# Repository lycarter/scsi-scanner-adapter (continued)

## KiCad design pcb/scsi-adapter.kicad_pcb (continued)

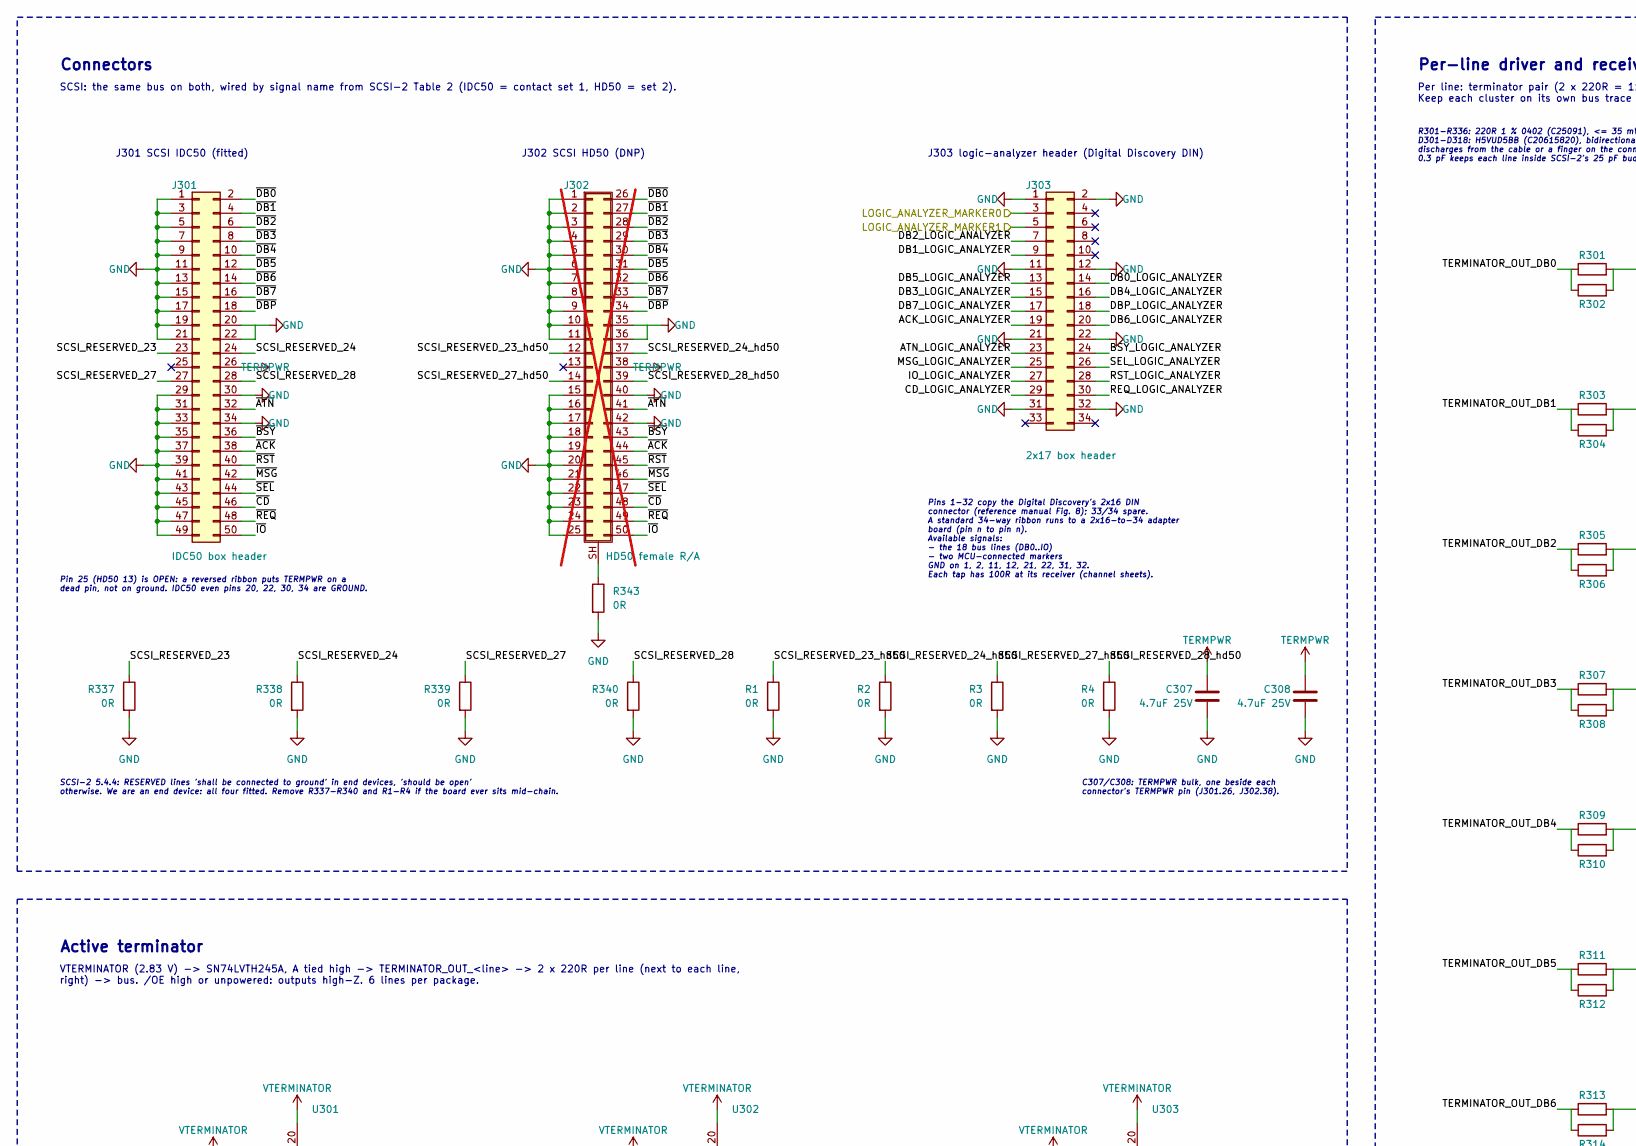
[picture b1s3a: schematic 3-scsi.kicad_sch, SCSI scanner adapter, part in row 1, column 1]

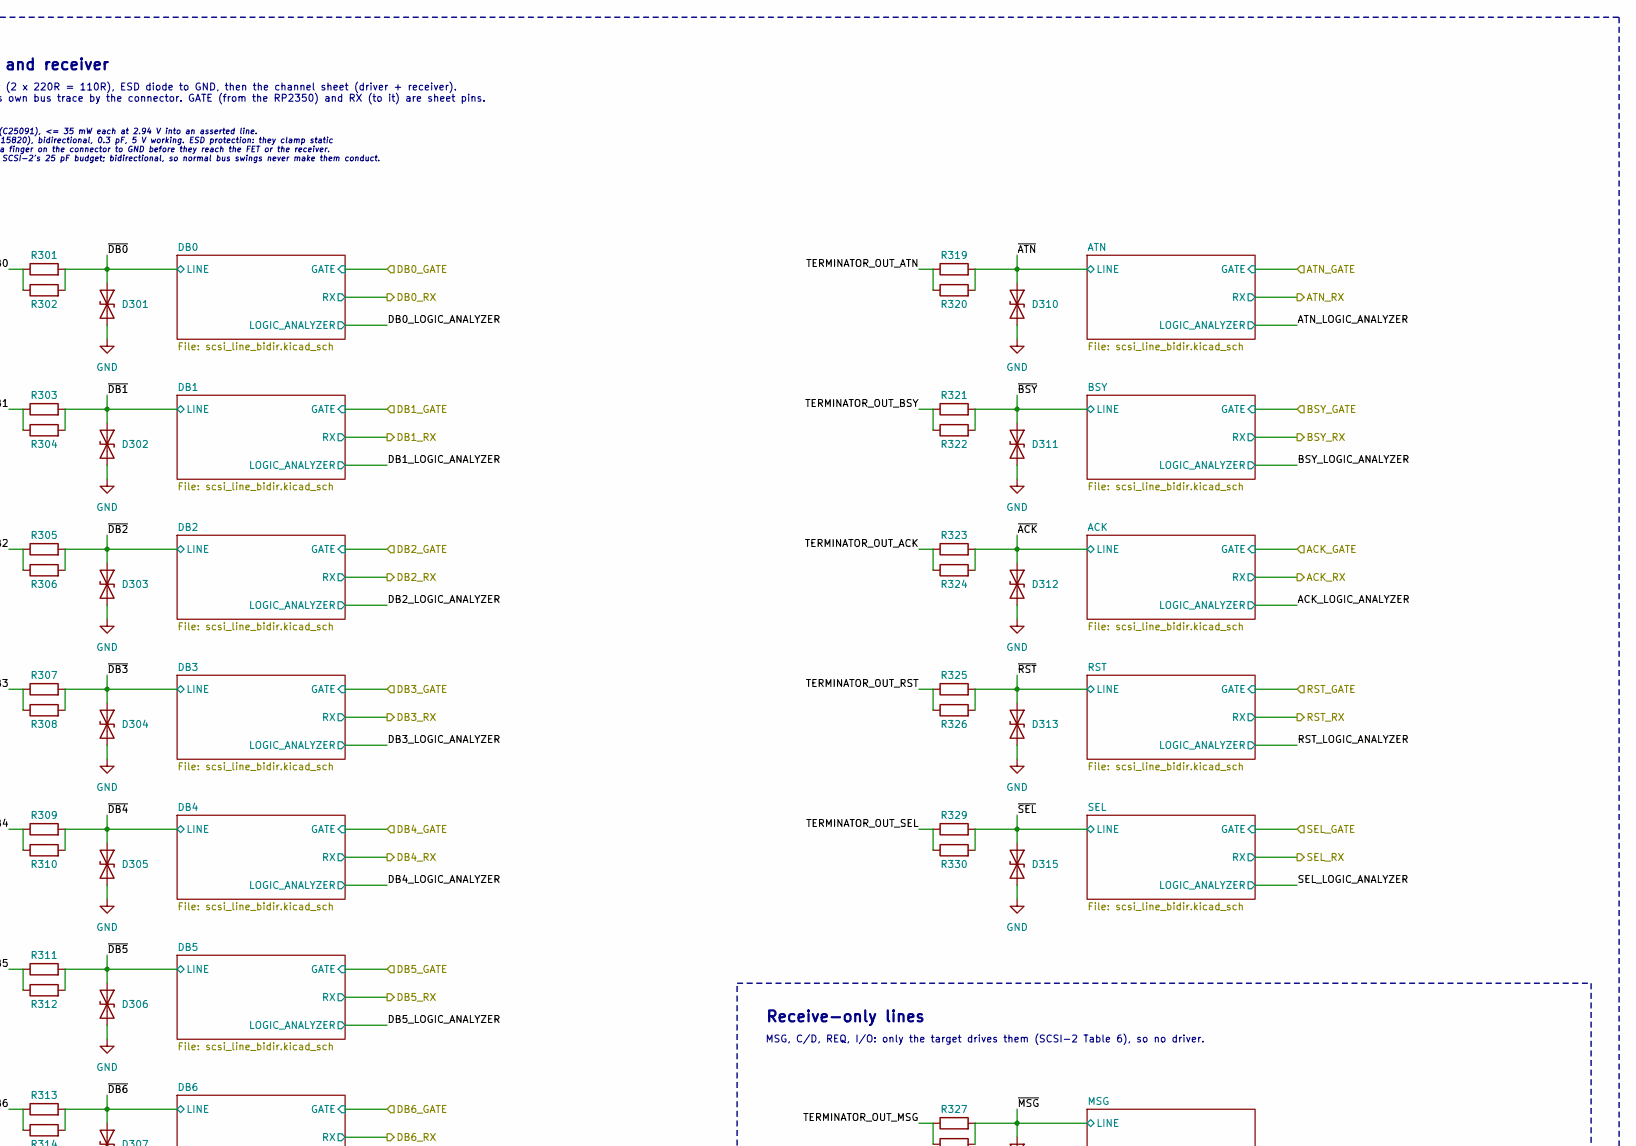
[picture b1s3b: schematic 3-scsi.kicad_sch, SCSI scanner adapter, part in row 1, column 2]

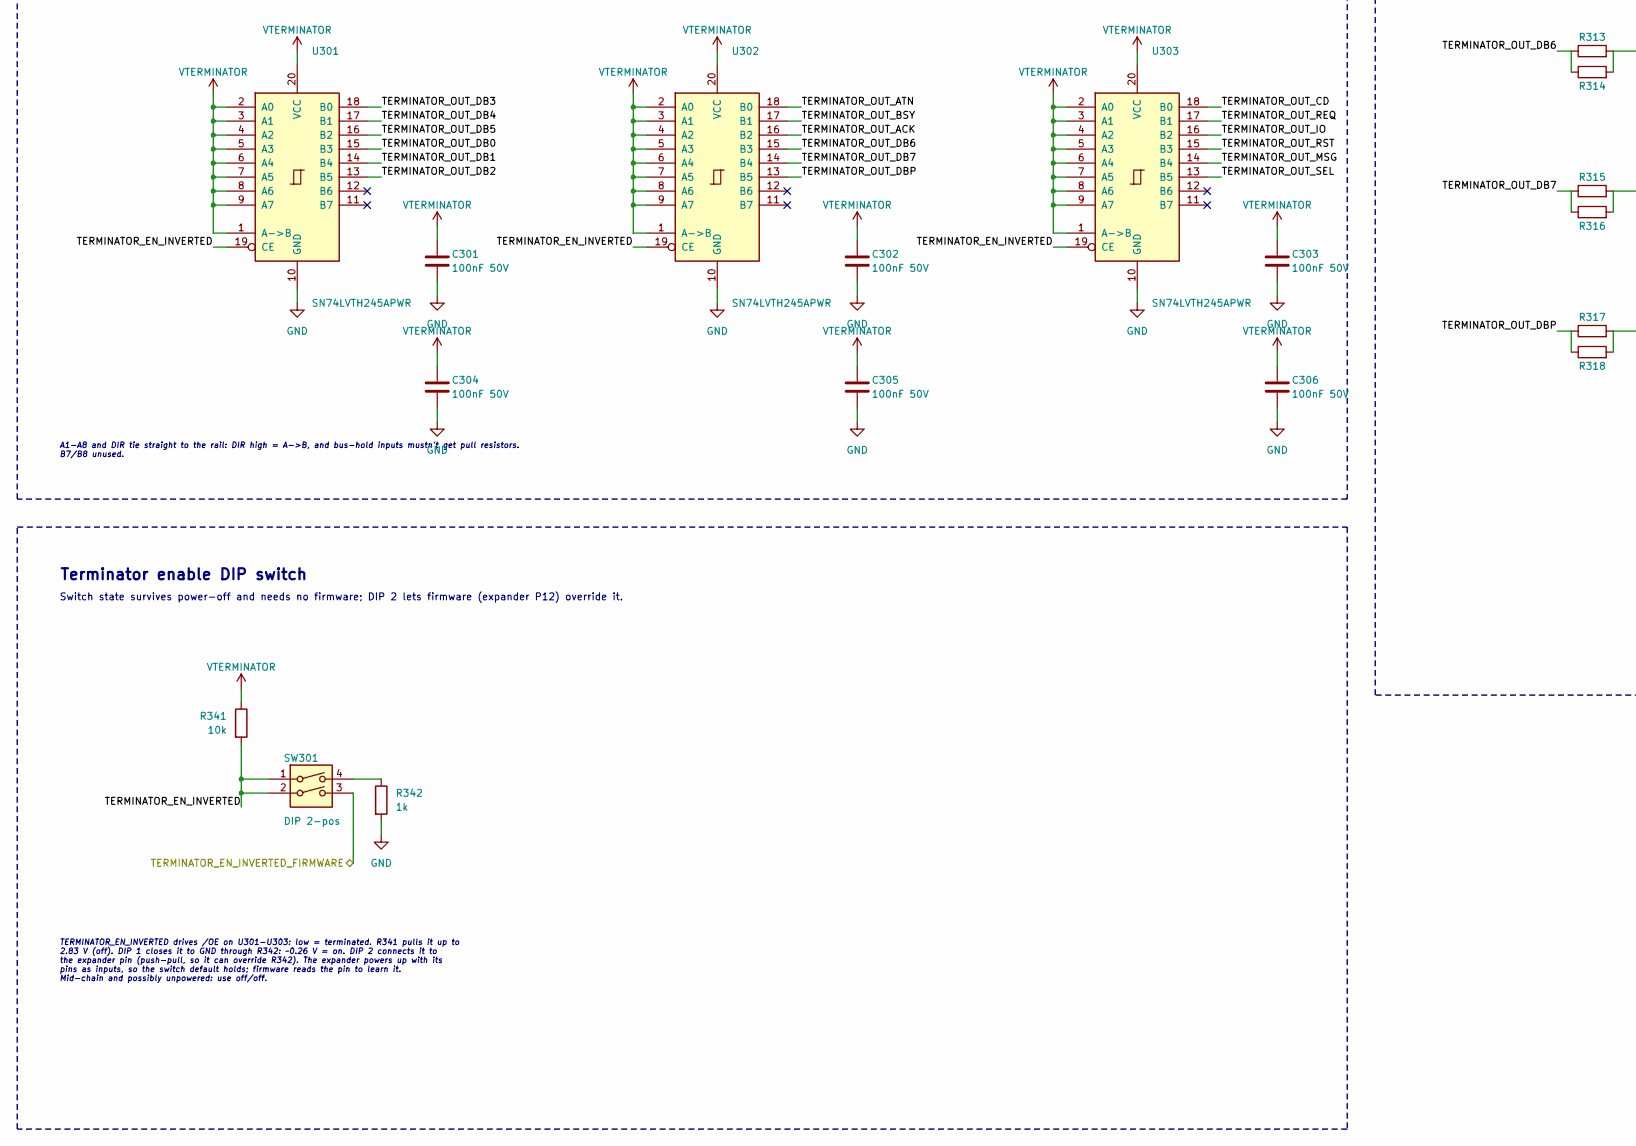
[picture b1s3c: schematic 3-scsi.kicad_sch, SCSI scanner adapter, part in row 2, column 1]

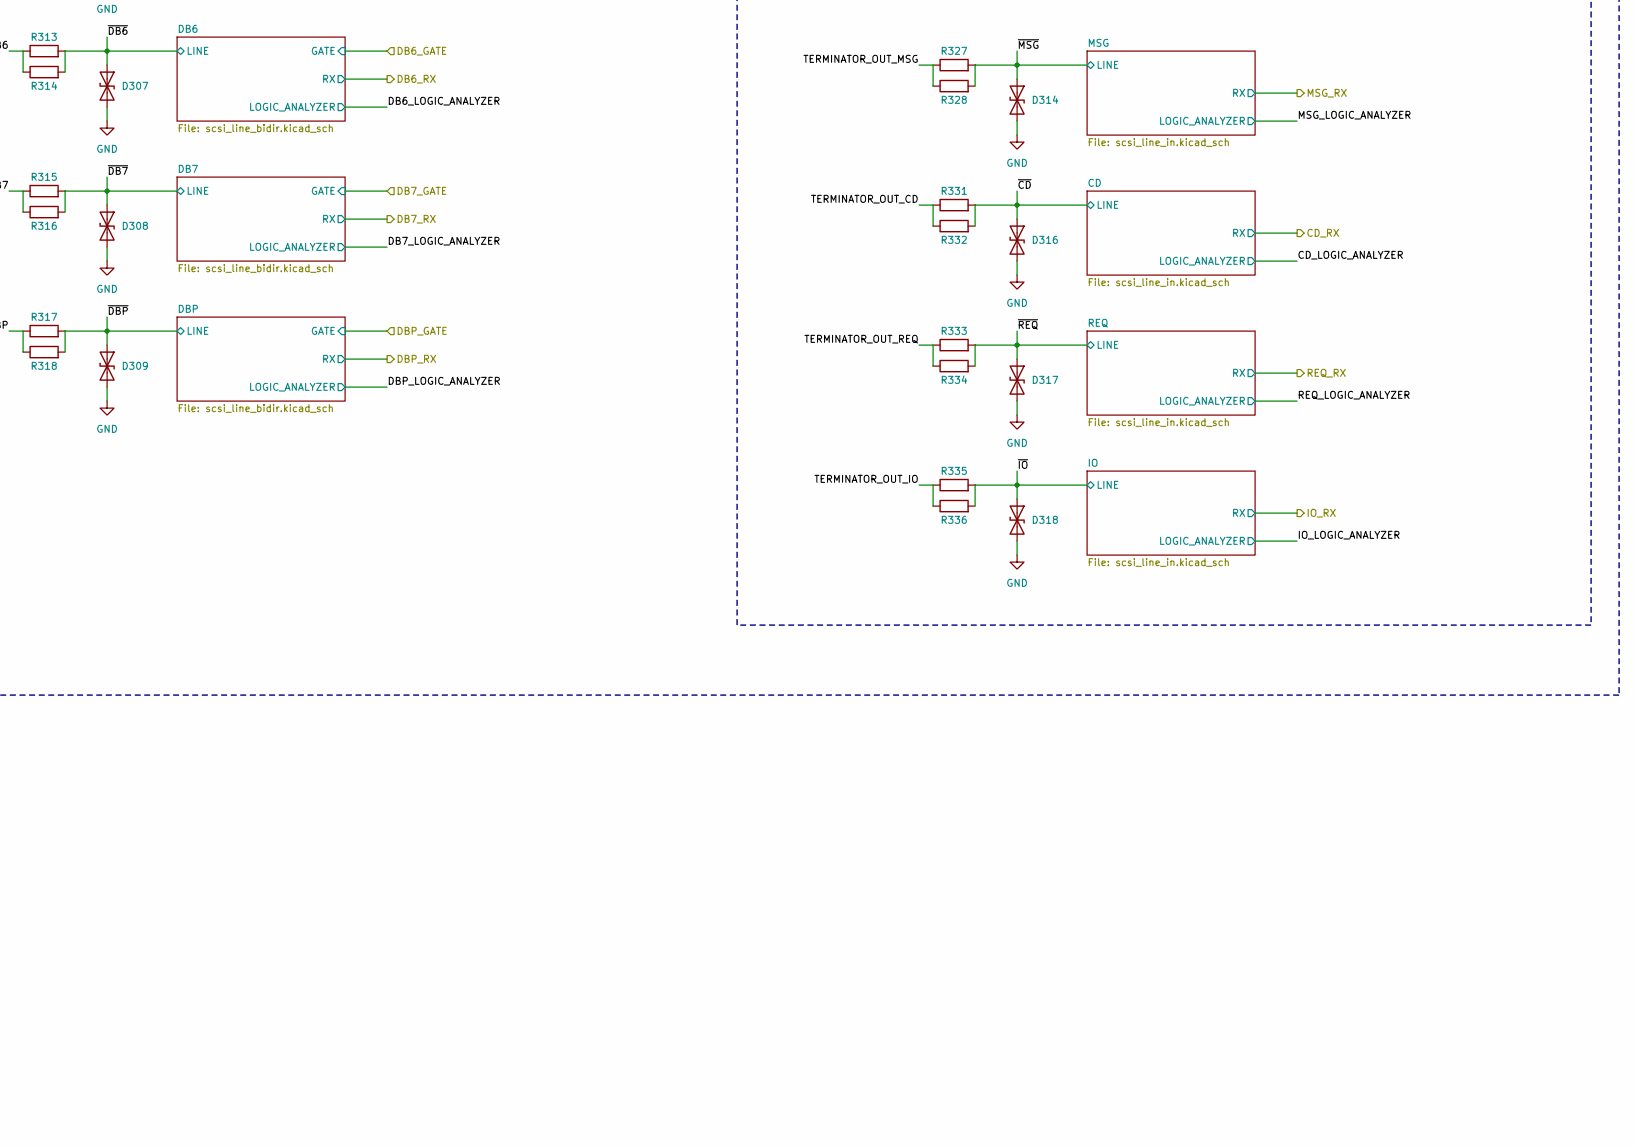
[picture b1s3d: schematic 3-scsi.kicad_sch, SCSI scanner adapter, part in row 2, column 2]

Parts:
C301, C302, C303, C304, C305, C306: 100nF 50V; C_0402_1005Metric; LCSC C307331
C307, C308: 4.7uF 25V; C_0805_2012Metric; LCSC C1779
D301, D302, D303, D304, D305, D306, D307, D308, D309, D310, D311, D312, D313, D314, D315, D316, D317, D318: H5VUD5BB; D_SOD-523; LCSC C20615820
J301: IDC50 box header; IDC-Header_2x25_P2.54mm_Vertical; LCSC C30006
J302: HD50 female R/A; TE_AMPLIMITE-050_5787082-5_50pos_P1.27mm_Horizontal; not fitted
J303: 2x17 box header; IDC-Header_2x17_P2.54mm_Vertical; LCSC C20920
R1, R2, R3, R4, R337, R338, R339, R340, R343: 0R; R_0402_1005Metric; LCSC C17168
R301, R302, R303, R304, R305, R306, R307, R308, R309, R310, R311, R312, R313, R314, R315, R316, R317, R318, R319, R320, R321, R322, R323, R324, R325, R326, R327, R328, R329, R330, R331, R332, R333, R334, R335, R336: 220R; R_0402_1005Metric; LCSC C25091
R341: 10k; R_0402_1005Metric; LCSC C25744
R342: 1k; R_0402_1005Metric; LCSC C11702
SW301: DIP 2-pos; SW_DIP_SPSTx02_Slide_SHOUHAN_2.54-2P-TPGT_W8.8mm_P2.54mm; LCSC C6331180
U301, U302, U303: SN74LVTH245APWR; TSSOP-20_4.4x6.5mm_P0.65mm; LCSC C2652121

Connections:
/LOGIC_ANALYZER_MARKER0: J303.3; also elsewhere on the board
/LOGIC_ANALYZER_MARKER1: J303.5; also elsewhere on the board
/TERMINATOR_EN_INVERTED_FIRMWARE: SW301.3; also elsewhere on the board
/scsi/ACK_LOGIC_ANALYZER: J303.19; also elsewhere on the board
/scsi/ATN_LOGIC_ANALYZER: J303.23; also elsewhere on the board
/scsi/BSY_LOGIC_ANALYZER: J303.24; also elsewhere on the board
/scsi/CD_LOGIC_ANALYZER: J303.29; also elsewhere on the board
/scsi/DB0_LOGIC_ANALYZER: J303.14; also elsewhere on the board
/scsi/DB1_LOGIC_ANALYZER: J303.9; also elsewhere on the board
/scsi/DB2_LOGIC_ANALYZER: J303.7; also elsewhere on the board
/scsi/DB3_LOGIC_ANALYZER: J303.15; also elsewhere on the board
/scsi/DB4_LOGIC_ANALYZER: J303.16; also elsewhere on the board
/scsi/DB5_LOGIC_ANALYZER: J303.13; also elsewhere on the board
/scsi/DB6_LOGIC_ANALYZER: J303.20; also elsewhere on the board
/scsi/DB7_LOGIC_ANALYZER: J303.17; also elsewhere on the board
/scsi/DBP_LOGIC_ANALYZER: J303.18; also elsewhere on the board
/scsi/IO_LOGIC_ANALYZER: J303.27; also elsewhere on the board
/scsi/MSG_LOGIC_ANALYZER: J303.25; also elsewhere on the board
/scsi/REQ_LOGIC_ANALYZER: J303.30; also elsewhere on the board
/scsi/RST_LOGIC_ANALYZER: J303.28; also elsewhere on the board
/scsi/SCSI_RESERVED_23: J301.23, R337.1
/scsi/SCSI_RESERVED_23_hd50: J302.12, R1.1
/scsi/SCSI_RESERVED_24: J301.24, R338.1
/scsi/SCSI_RESERVED_24_hd50: J302.37, R2.1
/scsi/SCSI_RESERVED_27: J301.27, R339.1
/scsi/SCSI_RESERVED_27_hd50: J302.14, R3.1
/scsi/SCSI_RESERVED_28: J301.28, R340.1
/scsi/SCSI_RESERVED_28_hd50: J302.39, R4.1
/scsi/SEL_LOGIC_ANALYZER: J303.26; also elsewhere on the board
/scsi/TERMINATOR_EN_INVERTED: R341.2, SW301.1, SW301.2, U301.19 (CE), U302.19 (CE), U303.19 (CE)
/scsi/TERMINATOR_OUT_ACK: R323.1, R324.1, U302.16 (B2)
/scsi/TERMINATOR_OUT_ATN: R319.1, R320.1, U302.18 (B0)
/scsi/TERMINATOR_OUT_BSY: R321.1, R322.1, U302.17 (B1)
/scsi/TERMINATOR_OUT_CD: R331.1, R332.1, U303.18 (B0)
/scsi/TERMINATOR_OUT_DB0: R301.1, R302.1, U301.15 (B3)
/scsi/TERMINATOR_OUT_DB1: R303.1, R304.1, U301.14 (B4)
/scsi/TERMINATOR_OUT_DB2: R305.1, R306.1, U301.13 (B5)
/scsi/TERMINATOR_OUT_DB3: R307.1, R308.1, U301.18 (B0)
/scsi/TERMINATOR_OUT_DB4: R309.1, R310.1, U301.17 (B1)
/scsi/TERMINATOR_OUT_DB5: R311.1, R312.1, U301.16 (B2)
/scsi/TERMINATOR_OUT_DB6: R313.1, R314.1, U302.15 (B3)
/scsi/TERMINATOR_OUT_DB7: R315.1, R316.1, U302.14 (B4)
/scsi/TERMINATOR_OUT_DBP: R317.1, R318.1, U302.13 (B5)
/scsi/TERMINATOR_OUT_IO: R335.1, R336.1, U303.16 (B2)
/scsi/TERMINATOR_OUT_MSG: R327.1, R328.1, U303.14 (B4)
/scsi/TERMINATOR_OUT_REQ: R333.1, R334.1, U303.17 (B1)
/scsi/TERMINATOR_OUT_RST: R325.1, R326.1, U303.15 (B3)
/scsi/TERMINATOR_OUT_SEL: R329.1, R330.1, U303.13 (B5)
/scsi/~ACK: D312.1 (A1), J301.38, J302.44, R323.2, R324.2; also elsewhere on the board
/scsi/~ATN: D310.1 (A1), J301.32, J302.41, R319.2, R320.2; also elsewhere on the board
/scsi/~BSY: D311.1 (A1), J301.36, J302.43, R321.2, R322.2; also elsewhere on the board
/scsi/~CD: D316.1 (A1), J301.46, J302.48, R331.2, R332.2; also elsewhere on the board
/scsi/~DB0: D301.1 (A1), J301.2, J302.26, R301.2, R302.2; also elsewhere on the board
/scsi/~DB1: D302.1 (A1), J301.4, J302.27, R303.2, R304.2; also elsewhere on the board
/scsi/~DB2: D303.1 (A1), J301.6, J302.28, R305.2, R306.2; also elsewhere on the board
/scsi/~DB3: D304.1 (A1), J301.8, J302.29, R307.2, R308.2; also elsewhere on the board
/scsi/~DB4: D305.1 (A1), J301.10, J302.30, R309.2, R310.2; also elsewhere on the board
/scsi/~DB5: D306.1 (A1), J301.12, J302.31, R311.2, R312.2; also elsewhere on the board
/scsi/~DB6: D307.1 (A1), J301.14, J302.32, R313.2, R314.2; also elsewhere on the board
/scsi/~DB7: D308.1 (A1), J301.16, J302.33, R315.2, R316.2; also elsewhere on the board
/scsi/~DBP: D309.1 (A1), J301.18, J302.34, R317.2, R318.2; also elsewhere on the board
/scsi/~IO: D318.1 (A1), J301.50, J302.50, R335.2, R336.2; also elsewhere on the board
/scsi/~MSG: D314.1 (A1), J301.42, J302.46, R327.2, R328.2; also elsewhere on the board
/scsi/~REQ: D317.1 (A1), J301.48, J302.49, R333.2, R334.2; also elsewhere on the board
/scsi/~RST: D313.1 (A1), J301.40, J302.45, R325.2, R326.2; also elsewhere on the board
/scsi/~SEL: D315.1 (A1), J301.44, J302.47, R329.2, R330.2; also elsewhere on the board
GND: C301.2, C302.2, C303.2, C304.2, C305.2, C306.2, C307.2, C308.2, D301.2 (A2), D302.2 (A2), D303.2 (A2), D304.2 (A2), D305.2 (A2), D306.2 (A2), D307.2 (A2), D308.2 (A2), D309.2 (A2), D310.2 (A2), D311.2 (A2), D312.2 (A2), D313.2 (A2), D314.2 (A2), D315.2 (A2), D316.2 (A2), D317.2 (A2), D318.2 (A2), J301.1, J301.3, J301.5, J301.7, J301.9, J301.11, J301.13, J301.15, J301.17, J301.19, J301.20, J301.21, J301.22, J301.29, J301.30, J301.31, J301.33, J301.34, J301.35, J301.37, J301.39, J301.41, J301.43, J301.45, J301.47, J301.49, J302.1, J302.2, J302.3, J302.4, J302.5, J302.6, J302.7, J302.8, J302.9, J302.10, J302.11, J302.15, J302.16, J302.17, J302.18, J302.19, J302.20, J302.21, J302.22, J302.23, J302.24, J302.25, J302.35, J302.36, J302.40, J302.42, J303.1, J303.2, J303.11, J303.12, J303.21, J303.22, J303.31, J303.32, R1.2, R2.2, R3.2, R4.2, R337.2, R338.2, R339.2, R340.2, R342.2, R343.2, U301.10 (GND), U302.10 (GND), U303.10 (GND); also elsewhere on the board
unnamed: J302.SH (Shield), R343.1
unnamed: R342.1, SW301.4
TERMPWR: C307.1, C308.1, J301.26, J302.38; also elsewhere on the board
VTERMINATOR: C301.1, C302.1, C303.1, C304.1, C305.1, C306.1, R341.1, U301.1 (A->B), U301.2 (A0), U301.3 (A1), U301.4 (A2), U301.5 (A3), U301.6 (A4), U301.7 (A5), U301.8 (A6), U301.9 (A7), U301.20 (VCC), U302.1 (A->B), U302.2 (A0), U302.3 (A1), U302.4 (A2), U302.5 (A3), U302.6 (A4), U302.7 (A5), U302.8 (A6), U302.9 (A7), U302.20 (VCC), U303.1 (A->B), U303.2 (A0), U303.3 (A1), U303.4 (A2), U303.5 (A3), U303.6 (A4), U303.7 (A5), U303.8 (A6), U303.9 (A7), U303.20 (VCC); also elsewhere on the board

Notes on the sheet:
Pins 1-32 copy the Digital Discovery's 2x16 DIN connector (reference manual Fig. 8); 33/34 spare. A standard 34-way ribbon runs to a 2x16-to-34 adapter board (pin n to pin n). Available signals: - the 18 bus lines (DB0..IO) - two MCU-connected markers GND on 1, 2, 11, 12, 21, 22, 31, 32. Each tap h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
SCSI: the same bus on both, wired by signal name from SCSI-2 Table 2 (IDC50 = contact set 1, HD50 = set 2).
Receive-only lines
Connectors
Active terminator
R301-R336: 220R 1 % 0402 (C25091), <= 35 mW each at 2.94 V into an asserted line. D301-D318: H5VUD5BB (C20615820), bidirectional, 0.3 pF, 5 V working. ESD protection: they clamp static discharges from the cable or a finger on the connector to GND before they reach the FET or the receiver. 0.3 pF ke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
Pin 25 (HD50 13) is OPEN: a reversed ribbon puts TERMPWR on a dead pin, not on ground. IDC50 even pins 20, 22, 30, 34 are GROUND.
SCSI-2 5.4.4: RESERVED lines 'shall be connected to ground' in end devices, 'should be open' otherwise. We are an end device: all four fitted. Remove R337-R340 and R1-R4 if the board ever sits mid-chain.
Per line: terminator pair (2 x 220R = 110R), ESD diode to GND, then the channel sheet (driver + receiver). Keep each cluster on its own bus trace by the connector. GATE (from the RP2350) and RX (to it) are sheet pins.
Switch state survives power-off and needs no firmware; DIP 2 lets firmware (expander P12) override it.
A1-A8 and DIR tie straight to the rail: DIR high = A->B, and bus-hold inputs mustn't get pull resistors. B7/B8 unused.
Terminator enable DIP switch
J303 logic-analyzer header (Digital Discovery DIN)
TERMINATOR_EN_INVERTED drives /OE on U301-U303: low = terminated. R341 pulls it up to 2.83 V (off). DIP 1 closes it to GND through R342: ~0.26 V = on. DIP 2 connects it to the expander pin (push-pull, so it can override R342). The expander powers up with its pins as inputs, so the switch default ho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
J302 SCSI HD50 (DNP)
MSG, C/D, REQ, I/O: only the target drives them (SCSI-2 Table 6), so no driver.
VTERMINATOR (2.83 V) -> SN74LVTH245A, A tied high -> TERMINATOR_OUT_<line> -> 2 x 220R per line (next to each line, right) -> bus. /OE high or unpowered: outputs high-Z. 6 lines per package.
Per-line driver and receiver
J301 SCSI IDC50 (fitted)
C307/C308: TERMPWR bulk, one beside each connector's TERMPWR pin (J301.26, J302.38).

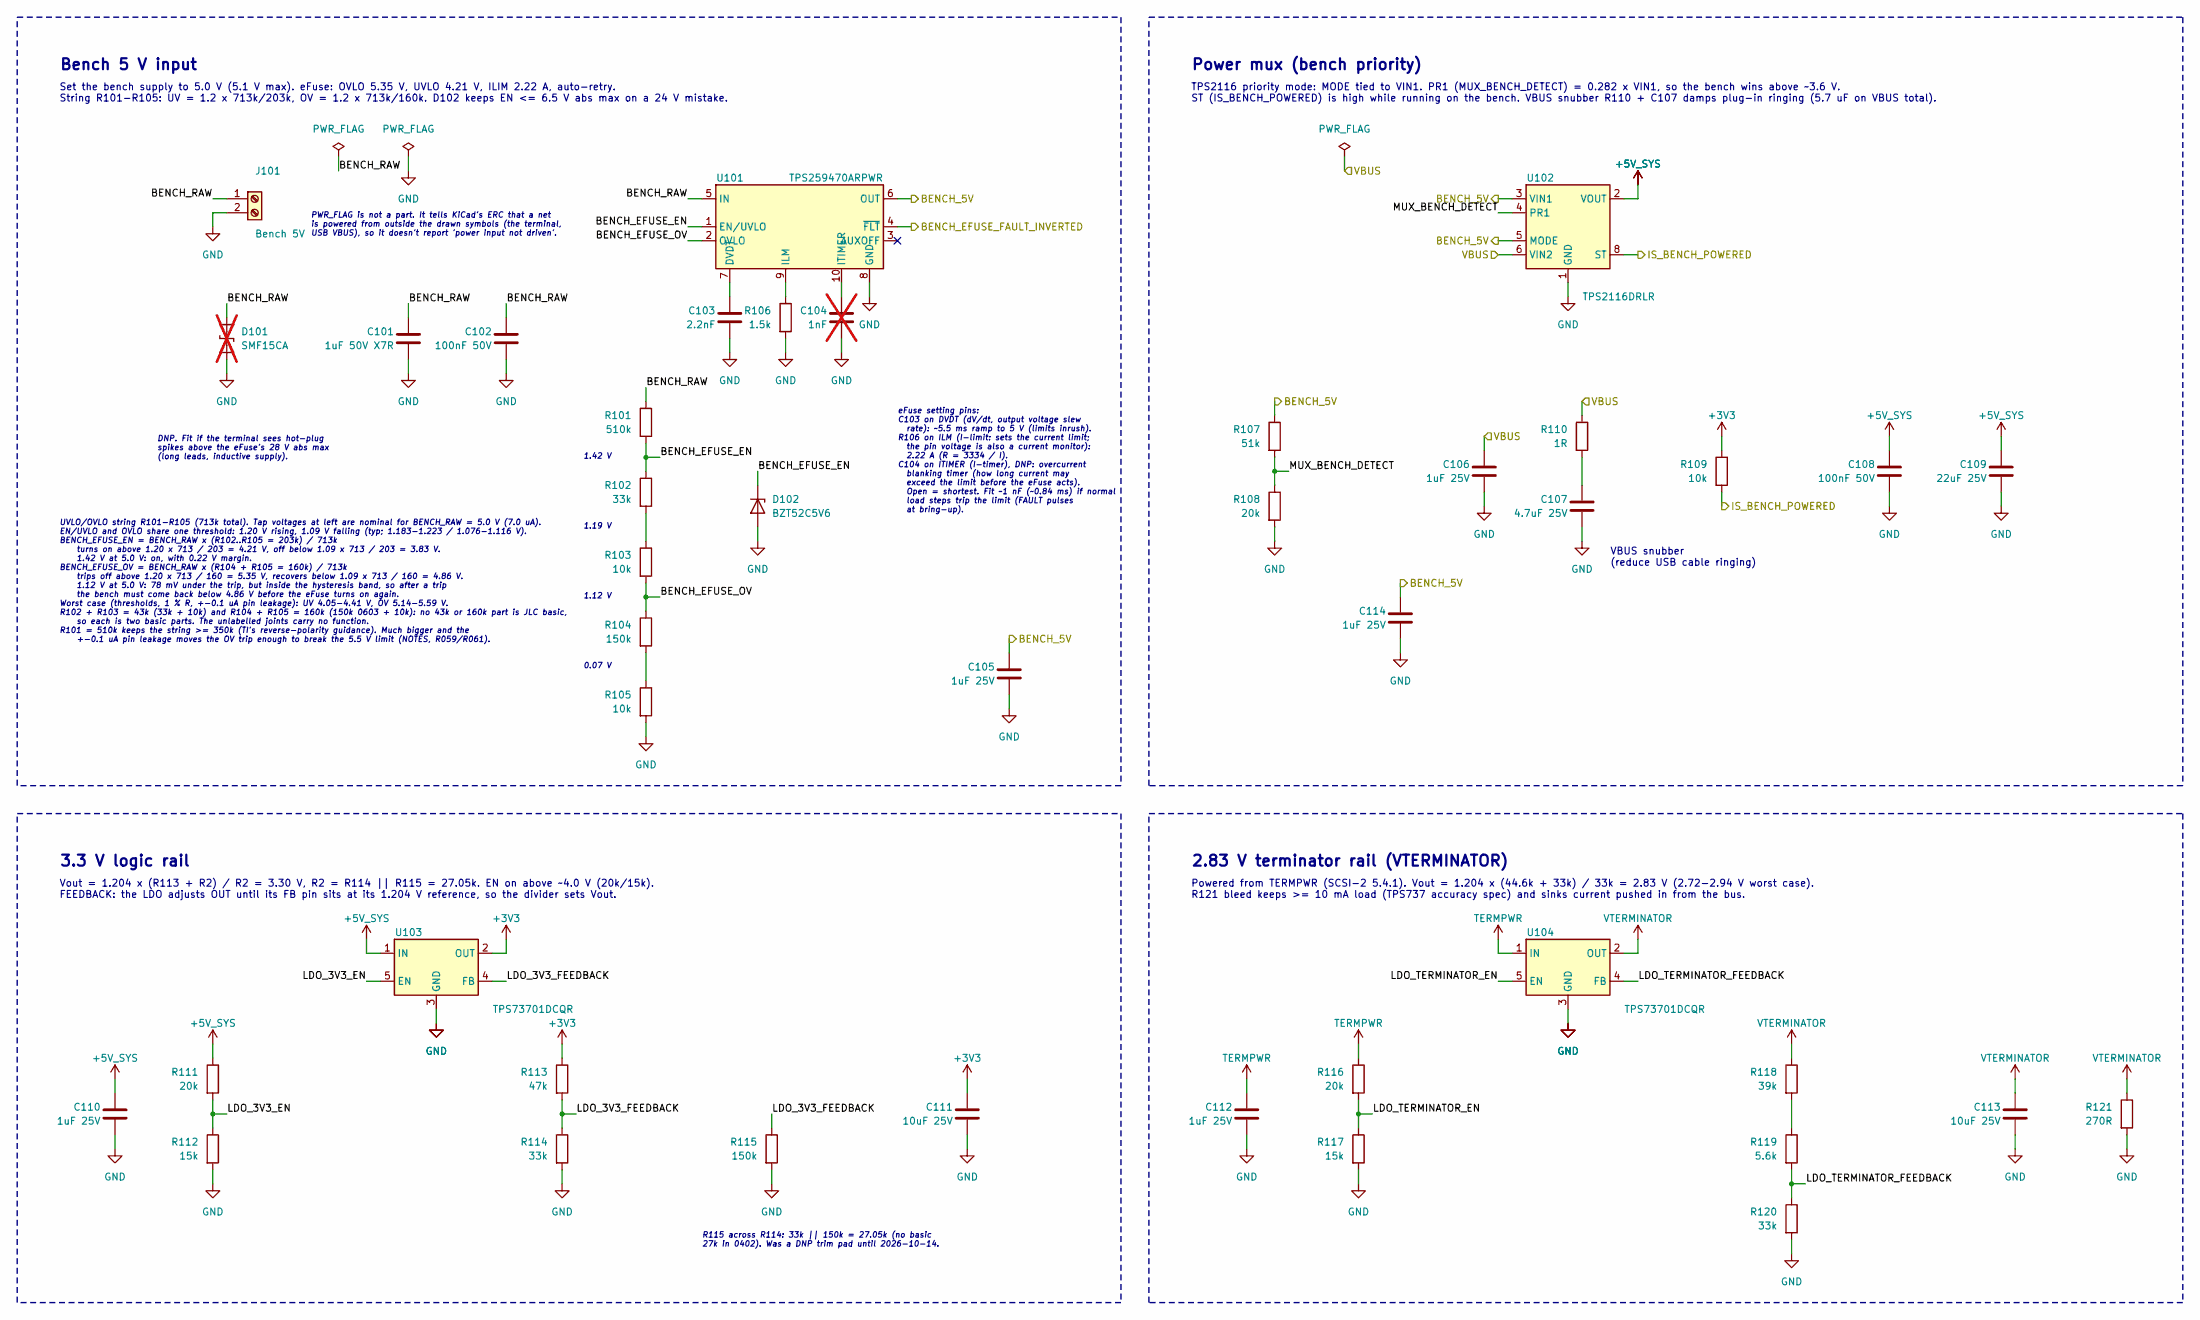
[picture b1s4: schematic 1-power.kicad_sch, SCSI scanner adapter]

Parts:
C101: 1uF 50V X7R; C_0805_2012Metric; LCSC C28323
C102, C108: 100nF 50V; C_0402_1005Metric; LCSC C307331
C103: 2.2nF; C_0603_1608Metric; LCSC C1604
C104: 1nF; C_0402_1005Metric; not fitted
C105, C106, C110, C112, C114: 1uF 25V; C_0402_1005Metric; LCSC C52923
C107: 4.7uF 25V; C_0805_2012Metric; LCSC C1779
C109: 22uF 25V; C_0805_2012Metric; LCSC C45783
C111, C113: 10uF 25V; C_0805_2012Metric; LCSC C15850
D101: SMF15CA; D_SOD-123F; LCSC C19077510; not fitted
D102: BZT52C5V6; D_SOD-123; LCSC C19077402
J101: Bench 5V; TerminalBlock_Kangnex_WJ500V-5.08-2P_1x02_P5.08mm_Horizontal; LCSC C8465
R101: 510k; R_0603_1608Metric; LCSC C23192
R102, R114, R120: 33k; R_0402_1005Metric; LCSC C25779
R103, R105, R109: 10k; R_0402_1005Metric; LCSC C25744
R104, R115: 150k; R_0603_1608Metric; LCSC C22807
R106: 1.5k; R_0402_1005Metric; LCSC C25867
R107: 51k; R_0402_1005Metric; LCSC C25794
R108, R111, R116: 20k; R_0402_1005Metric; LCSC C25765
R110: 1R; R_0603_1608Metric; LCSC C22936
R112, R117: 15k; R_0402_1005Metric; LCSC C25756
R113: 47k; R_0402_1005Metric; LCSC C25792
R118: 39k; R_0603_1608Metric; LCSC C23153
R119: 5.6k; R_0603_1608Metric; LCSC C23189
R121: 270R; R_0603_1608Metric; LCSC C22966
U101: TPS259470ARPWR; Texas_RPW0010A_VQFN-HR-10_2x2mm_P0.45mm; LCSC C3662799
U102: TPS2116DRLR; SOT-583-8; LCSC C3235557
U103, U104: TPS73701DCQR; SOT-223-6; LCSC C56848

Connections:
+3V3: C111.1, R109.1, R113.1, U103.2 (OUT); also elsewhere on the board
+5V_SYS: C108.1, C109.1, C110.1, R111.1, U102.2 (VOUT), U102.7 (VOUT), U103.1 (IN); also elsewhere on the board
/BENCH_5V: C105.1, C114.1, R107.1, U101.6 (OUT), U102.3 (VIN1), U102.5 (MODE); also elsewhere on the board
/BENCH_EFUSE_FAULT_INVERTED: U101.4 (~FLT); also elsewhere on the board
/IS_BENCH_POWERED: R109.2, U102.8 (ST); also elsewhere on the board
/VBUS: C106.1, R110.1, U102.6 (VIN2); also elsewhere on the board
/power/BENCH_EFUSE_EN: D102.1 (K), R101.2, R102.1, U101.1 (EN/UVLO)
/power/BENCH_EFUSE_OV: R103.2, R104.1, U101.2 (OVLO)
/power/BENCH_RAW: C101.1, C102.1, D101.1 (A1), J101.1, R101.1, U101.5 (IN)
/power/LDO_3V3_EN: R111.2, R112.1, U103.5 (EN)
/power/LDO_3V3_FEEDBACK: R113.2, R114.1, R115.1, U103.4 (FB)
/power/LDO_TERMINATOR_EN: R116.2, R117.1, U104.5 (EN)
/power/LDO_TERMINATOR_FEEDBACK: R119.2, R120.1, U104.4 (FB)
/power/MUX_BENCH_DETECT: R107.2, R108.1, U102.4 (PR1)
GND: C101.2, C102.2, C103.2, C104.2, C105.2, C106.2, C107.2, C108.2, C109.2, C110.2, C111.2, C112.2, C113.2, C114.2, D101.2 (A2), D102.2 (A), J101.2, R105.2, R106.2, R108.2, R112.2, R114.2, R115.2, R117.2, R120.2, R121.2, U101.8 (GND), U102.1 (GND), U103.3 (GND), U103.6 (GND), U104.3 (GND), U104.6 (GND); also elsewhere on the board
unnamed: C107.1, R110.2
unnamed: R102.2, R103.1
unnamed: R104.2, R105.1
unnamed: R118.2, R119.1
unnamed: C103.1, U101.7 (DVDT)
unnamed: R106.1, U101.9 (ILM)
unnamed: C104.1, U101.10 (ITIMER)
TERMPWR: C112.1, R116.1, U104.1 (IN); also elsewhere on the board
VTERMINATOR: C113.1, R118.1, R121.1, U104.2 (OUT); also elsewhere on the board

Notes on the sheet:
0.07 V
1.12 V
R115 across R114: 33k || 150k = 27.05k (no basic 27k in 0402). Was a DNP trim pad until 2026-10-14.
Powered from TERMPWR (SCSI-2 5.4.1). Vout = 1.204 x (44.6k + 33k) / 33k = 2.83 V (2.72-2.94 V worst case). R121 bleed keeps >= 10 mA load (TPS737 accuracy spec) and sinks current pushed in from the bus.
3.3 V logic rail
Bench 5 V input
Set the bench supply to 5.0 V (5.1 V max). eFuse: OVLO 5.35 V, UVLO 4.21 V, ILIM 2.22 A, auto-retry. String R101-R105: UV = 1.2 x 713k/203k, OV = 1.2 x 713k/160k. D102 keeps EN <= 6.5 V abs max on a 24 V mistake.
UVLO/OVLO string R101-R105 (713k total). Tap voltages at left are nominal for BENCH_RAW = 5.0 V (7.0 uA). EN/UVLO and OVLO share one threshold: 1.20 V rising, 1.09 V falling (typ; 1.183-1.223 / 1.076-1.116 V). BENCH_EFUSE_EN = BENCH_RAW x (R102..R105 = 203k) / 713k turns on above 1.20 x 713 / 203 =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
PWR_FLAG is not a part. It tells KiCad's ERC that a net is powered from outside the drawn symbols (the terminal, USB VBUS), so it doesn't report 'power input not driven'.
eFuse setting pins: C103 on DVDT (dV/dt, output voltage slew rate): ~5.5 ms ramp to 5 V (limits inrush). R106 on ILM (I-limit: sets the current limit; the pin voltage is also a current monitor): 2.22 A (R = 3334 / I). C104 on ITIMER (I-timer), DNP: overcurrent blanking timer (how long current may e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
1.42 V
2.83 V terminator rail (VTERMINATOR)
Power mux (bench priority)
Vout = 1.204 x (R113 + R2) / R2 = 3.30 V, R2 = R114 || R115 = 27.05k. EN on above ~4.0 V (20k/15k). FEEDBACK: the LDO adjusts OUT until its FB pin sits at its 1.204 V reference, so the divider sets Vout.
TPS2116 priority mode: MODE tied to VIN1. PR1 (MUX_BENCH_DETECT) = 0.282 x VIN1, so the bench wins above ~3.6 V. ST (IS_BENCH_POWERED) is high while running on the bench. VBUS snubber R110 + C107 damps plug-in ringing (5.7 uF on VBUS total).
DNP. Fit if the terminal sees hot-plug spikes above the eFuse's 28 V abs max (long leads, inductive supply).
1.19 V
VBUS snubber (reduce USB cable ringing)
